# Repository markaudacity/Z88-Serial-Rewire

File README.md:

# Z88 Internal DE-9 Cap/Resistor Board

The Z88 has several resistors and capacitors on the seriL port lines, presumably for EMI filtration. On earlier machines, these are soldered dead-bug style directly to the connector pins and shell, which makes my plan to re-wire it to RS-232 pinout a bit fussy. 
My newer-production Z88 has a small PCB soldered to the back of the DE-9 connector with the resistors and bypass/filter caps, which makes changing the pinout much easier to implement.

I have included KiCad projects for both the original pinout with a DE-9F and the RS-232 pinout with a DE-9M.

# Current Status
This is the initial version of this project, yet to be build and thus provided with no warranty, assurances, promises, rumors, innuendos, or otherwise implications about its functionality or fitness for purpose. I have ordered boards for both versions and will report back to the community on the [ZX World forums](www.sinclairzxworld.com), the [Z88 Telegram channel](t.me/cambridgez88), and likely the [Vintage Computer Federation forum](forum.vcfed.org) as well.

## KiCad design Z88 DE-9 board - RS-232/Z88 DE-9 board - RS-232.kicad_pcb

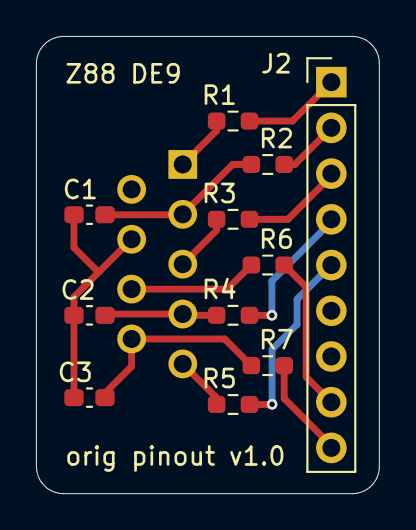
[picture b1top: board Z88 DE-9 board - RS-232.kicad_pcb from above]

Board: 2 copper layers, 19.0 x 25.4 mm, 12 parts (1 on the bottom side), 15 nets.

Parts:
C1, C2, C3: C; C_0603_1608Metric_Pad1.08x0.95mm_HandSolder
J1: DE-9 PCB Mount; DSUB-9_Female_Vertical_P2.77x2.84mm
J2: D header; PinHeader_1x09_P2.54mm_Vertical
R1, R3, R4, R7: 10k; R_0603_1608Metric_Pad0.98x0.95mm_HandSolder
R2, R5: 1k; R_0603_1608Metric_Pad0.98x0.95mm_HandSolder
R6: 470; R_0603_1608Metric_Pad0.98x0.95mm_HandSolder

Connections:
unnamed: J1.1, R1.1
unnamed: C1.1, J1.2, R2.1
unnamed: J1.3, R3.1
unnamed: C2.1, J1.4, R4.1
unnamed: J1.5, R5.1
unnamed: C1.2, C2.2, C3.1, J1.7
unnamed: J1.8, R6.1
unnamed: C3.2, J1.9, R7.1
unnamed: J2.1, R1.2
unnamed: J2.2, R2.2
unnamed: J2.3, R3.2
unnamed: J2.4, R4.2
unnamed: J2.5, R5.2
unnamed: J2.8, R6.2
unnamed: J2.9, R7.2

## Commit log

2025-01-03 fill README.md
2025-01-03 labeled DE-9 pins in schematic
2025-01-03 changed single-row header to dual so IDC connector can be used, replaced DE-9 footprint with custom to remove overhanging silkscreen
2025-01-10 del DS_Store
2026-03-19 Update fp-info-cache
2026-03-19 minor schematic tweaks
